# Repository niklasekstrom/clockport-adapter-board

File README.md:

# Clockport adapter board

A simple adapter pcb that connects to the 2 mm clockport connector on an Amiga,
via voltage level converters (5V↔3.3V), to a 2.54 mm pin header.

This can be useful for experimenting with connecting 3.3V devices
to the clockport.

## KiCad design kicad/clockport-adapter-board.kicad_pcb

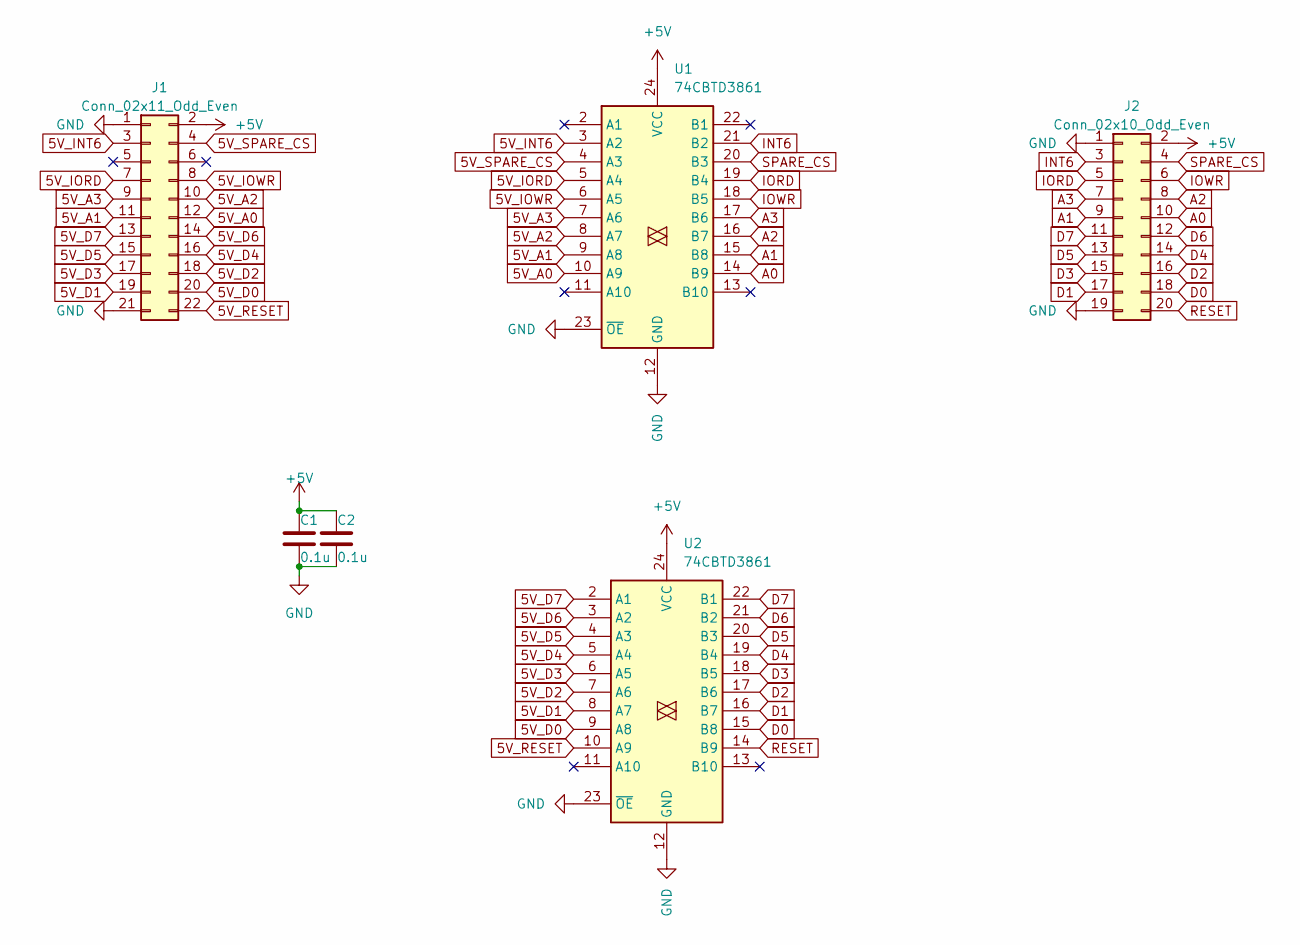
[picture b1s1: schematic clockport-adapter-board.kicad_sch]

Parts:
C1, C2: 0.1u; C_0603_1608Metric
J1: Conn_02x11_Odd_Even; PinSocket_2x11_P2.00mm_Vertical
J2: Conn_02x10_Odd_Even; PinHeader_2x10_P2.54mm_Vertical
U1, U2: 74CBTD3861; TSSOP-24_4.4x7.8mm_P0.65mm

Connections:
5V_A0: J1.12, U1.10 (A9)
5V_A1: J1.11, U1.9 (A8)
5V_A2: J1.10, U1.8 (A7)
5V_A3: J1.9, U1.7 (A6)
5V_D0: J1.20, U2.9 (A8)
5V_D1: J1.19, U2.8 (A7)
5V_D2: J1.18, U2.7 (A6)
5V_D3: J1.17, U2.6 (A5)
5V_D4: J1.16, U2.5 (A4)
5V_D5: J1.15, U2.4 (A3)
5V_D6: J1.14, U2.3 (A2)
5V_D7: J1.13, U2.2 (A1)
5V_INT6: J1.3, U1.3 (A2)
5V_IORD: J1.7, U1.5 (A4)
5V_IOWR: J1.8, U1.6 (A5)
5V_RESET: J1.22, U2.10 (A9)
5V_SPARE_CS: J1.4, U1.4 (A3)
+5V: C1.1, C2.1, J1.2, J2.2, U1.24 (VCC), U2.24 (VCC)
A0: J2.10, U1.14 (B9)
A1: J2.9, U1.15 (B8)
A2: J2.8, U1.16 (B7)
A3: J2.7, U1.17 (B6)
D0: J2.18, U2.15 (B8)
D1: J2.17, U2.16 (B7)
D2: J2.16, U2.17 (B6)
D3: J2.15, U2.18 (B5)
D4: J2.14, U2.19 (B4)
D5: J2.13, U2.20 (B3)
D6: J2.12, U2.21 (B2)
D7: J2.11, U2.22 (B1)
GND: C1.2, C2.2, J1.1, J1.21, J2.1, J2.19, U1.12 (GND), U1.23 (~OE), U2.12 (GND), U2.23 (~OE)
INT6: J2.3, U1.21 (B2)
IORD: J2.5, U1.19 (B4)
IOWR: J2.6, U1.18 (B5)
RESET: J2.20, U2.14 (B9)
SPARE_CS: J2.4, U1.20 (B3)

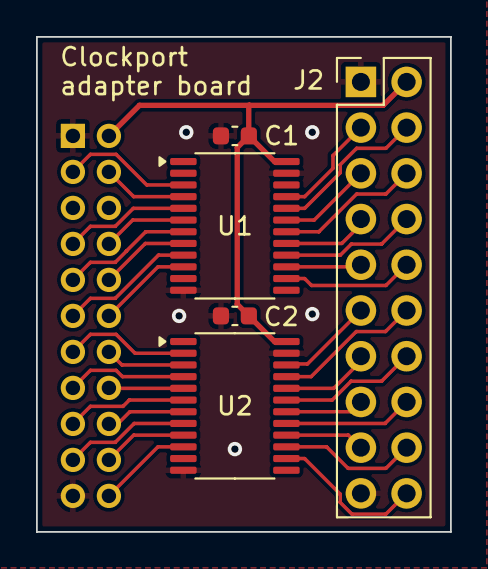
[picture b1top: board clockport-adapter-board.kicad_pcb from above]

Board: 2 copper layers, 23.0 x 27.5 mm, 6 parts (1 on the bottom side), 36 nets.
